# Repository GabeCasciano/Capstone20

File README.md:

# Capstone20

By: Gabriel Casciano, Niharika Shetty, Yasamin Ahmadzadeh, Mai Abdelhameed

------

An autonomous subsystem for a self-driving vehicle. Included in this project are the required software to interface with all of the autonomous sensors, algorithms and feedback loops which utilise the data from the sensors, and the different run-time applications which choose the specific algorithms for the given mode. 

------

## Project Structure

Outlined below is the structure of this repository and locations and purpose of each file, in the directories containing the specific files and the intermediary directories as well there are more files similar to this one which cover the specific files in more detail. Use this project structure below as a map for navigating through this repository.

- **AutonomousPkg**: The custom python package written for this project.
  - **Autonomous**: The top-level directory for the python package.
    - **Modules**: Contains all of the high-level algorithms required for this project.
      - **Obstacle_Detection.py**: This file implements an obstacle detection algorithm that is used to determine if obstacles obstruct the vehicles path, and determine their location relative to the vehicle.
      - **Obstacle_Avoidance.py**: This file implements an obstacle avoidance class and algorithm which simply navigates around the detected obstacle and returns the vehicle to its original path. 
      - **Path_Planning.py**: This file implements the primary path planning algorithm which generates the path, calculates the vehicles error and correction vector relative to the generated path.
      - **Sensor_Fusion.py**: This file implements a practical approach to an extended Kalman filter to fuse together GPS and IMU feedback into stable global coordinates and orientation. 
    - **Run**: Contains all of the run-times.
      - **ManualControl.py**: This file implements manual control via bluetooth controller connected to the base-station computer. It uses an *Arcade control scheme* which is similar to many video games where one joystick controls both power and steering.
      - **GPSAuto.py**: This file implements a simple GPS autonomous, when run the vehicle will navigate to its destination using only the onboard GPS.
      - **SFAuto.py**: This file implements the sensor fusion autonomous, where the vehicle will use its fused IMU and GPS data to navigate from point to point.
      - **FullAuto.py**: This file implements the full autonomous system, where it will use the sensor fusion for position and orientation feedback as well as the LIDAR to detect and avoid obstacles.
    - **Sensors**: Contains all of the sensor interfaces. Each interface implements a thread such that the sensor can be parsed and run concurrently to the rest of the system.
      - **Car**: Contains the interface and test files associated with the car.
        - **PS4_Controller**: Simple python thread used to read a bluetooth controller, meant for use with the manual control run-time.
        - **Car_Interface.py**: This file implements a thread which is used to communicate with the car's on board micro-controller, and provide it with instructions.
        - **Car_Test.py**: This file implements a simple test program which can be used to ensure the the *Car_Interface* is functioning correctly.
      - **GPS**: Contains all of the interface and test files associated with the GPS
        - **GPS_interface.py**: This file implements a thread which is used to parse information from the GPS, the thread is also responsible for formatting the GPS's data into appropriate data structures, providing control functions, as well as provide any conversion functions required. 
        - **GPS_Server.py**: This file implements a simple TCP server which is used to connect to the *GPS_Interface* remotely for control or to view what data is being parsed. 
        - **GPS_Test.py**: This file implements some simple tests to ensure that the *GPS_Interface* is working correctly.
      - **IMU**
        - **IMU_Interface.py**: This file implements a thread which is used to parse information from the IMU, the thread is responsible for formatting the IMU's data into appropriate data structures, as well as providing control functions.
        - **IMU_Server.py**: This file implements a simple TCP server which is used to connect to the *IMU_Interface* remotely for control or to view what data is being parsed.
        - **IMU_Test.py**: This file implements some simple tests to ensure that the *IMU_Interface* is working correctly.
      - **LIDAR**:
        - **LIDAR_Interface.py**: This file implements a thread which is used to parse information from the LIDAR, the thread is responsible for formatting the LIDAR's data into appropriate data structures, as well as providing control functions.
        - **LIDAR_Test.py**: This file implements some simple tests to ensure that the *LIDAR_Interface* is working correctly.
        - **LIDAR_Vis.py**: This file is used to visualise the data that the LIDAR  produces.
  - **build.sh** & **clear.sh**: These two scripts can be used to build the python package, and clear a pre-installed version of the package from the python environment.
  - misc. build and distribution files.
  
- **ControlSystem**: The PCB and software designed and written to test the implementation of our algorithms on a vehicle. This folder also includes all of the mechanical components that were designed for use with the specific car that used during the testing and implementation of this project.

- **Documents**: Implementation notes, diagrams, and documentation.

- **setup.sh**: This script can be used to install the required python packages into a python environment.

------

## Installation

To install the provided python package, python must first be [downloaded & installed](https://www.python.org/ftp/python/3.9.4/Python-3.9.4.tar.xz). 

**From snap:**

```bash
sudo add-apt-repository ppa:deadsnakes/ppa
sudo apt update
sudo apt install python3.9
```

**From source:**

```bash
wget -o https://www.python.org/ftp/python/3.9.4/Python-3.9.4.tar.xz
tar xf Python-3.9.4
cd Python-3.9.4/configure
make
sudo make install
```

------

After completing the installation of python navigate to the top-level folder of this repository (this folder) and run the following script which contains all the required commands to build and install the python package in your local python environment, the package can also be installed in a python venv.

If the folder has not yet been downloaded it can be cloned with git:

```bash
git clone https://github.com/GabeCasciano/Capstone20.git
```

After that:

```bash
cd Capstone20/
./setup.sh
```

------

## Running

After everything has been installed into the local python environment, running is as simple as calling the files, there are 2 ways in which this can be done

**Option 1**:

This option will run the run-time algorithm from the version installed in the local python environment

```bash
python3 -m Autonomous.Run.FullAuto
```

**Option 2**:

This option will run the run-time algorithm directly from the script itself:

```bash
cd Capstone20/AutonomousPkg/Autonomous/Run
python3 FullAuto.py
```

------

## Extending this package

Should you desire to fork this repository to continue our work or implement you own run-time algorithms, simply put the .py file in the folder `Capstone20/AutonomousPkg/Autonomous/Run`. Although technically the run-time algorithms can be run from any directory on your computer as the package installed in the local python environment, if the files are included in the *Run* directory they can be executed using the method provided in **Option 1** above.

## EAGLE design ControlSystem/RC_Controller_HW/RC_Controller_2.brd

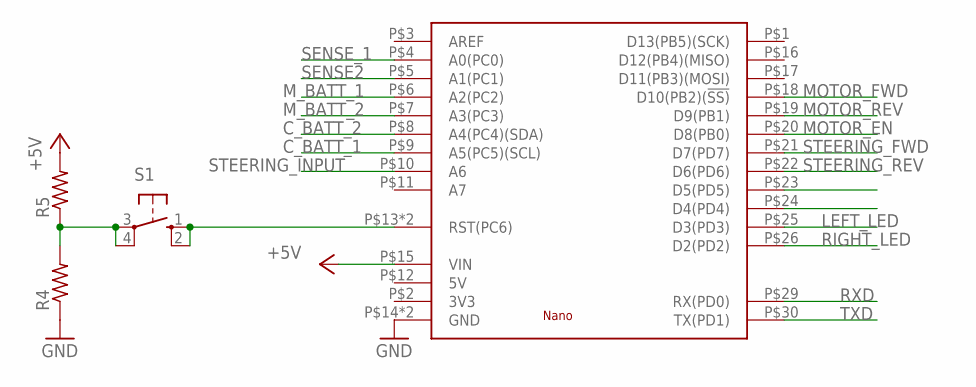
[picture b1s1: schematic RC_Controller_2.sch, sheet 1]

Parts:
R4, R5: R-US_R1206; R1206
S1: 10-XX; B3F-10XX
U$1: ARDUINO_NANO; NANO

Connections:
+5V: R5.2, U$1.P$15 (VIN); also elsewhere on the board
C_BATT_1: U$1.P$9 (A5(PC5)(SCL)); also elsewhere on the board
C_BATT_2: U$1.P$8 (A4(PC4)(SDA)); also elsewhere on the board
GND: R4.1, U$1.P$14 (GND), U$1.P$27 (GND); also elsewhere on the board
LEFT_LED: U$1.P$25 (D3(PD3)); also elsewhere on the board
MOTOR_EN: U$1.P$20 (D8(PB0)); also elsewhere on the board
MOTOR_FWD: U$1.P$18 (D10(PB2)(!SS)); also elsewhere on the board
MOTOR_REV: U$1.P$19 (D9(PB1)); also elsewhere on the board
M_BATT_1: U$1.P$6 (A2(PC2)); also elsewhere on the board
M_BATT_2: U$1.P$7 (A3(PC3)); also elsewhere on the board
unnamed: S1.1 (S), S1.2 (S1), U$1.P$13 (RST(PC6)), U$1.P$28 (RST(PC6))
unnamed: R4.2, R5.1, S1.3, S1.4 (P1)
RIGHT_LED: U$1.P$26 (D2(PD2)); also elsewhere on the board
RXD: U$1.P$29 (RX(PD0)); also elsewhere on the board
SENSE2: U$1.P$5 (A1(PC1)); also elsewhere on the board
SENSE_1: U$1.P$4 (A0(PC0)); also elsewhere on the board
STEERING_FWD: U$1.P$21 (D7(PD7)); also elsewhere on the board
STEERING_INPUT: U$1.P$10 (A6); also elsewhere on the board
STEERING_REV: U$1.P$22 (D6(PD6)); also elsewhere on the board
TXD: U$1.P$30 (TX(PD1)); also elsewhere on the board

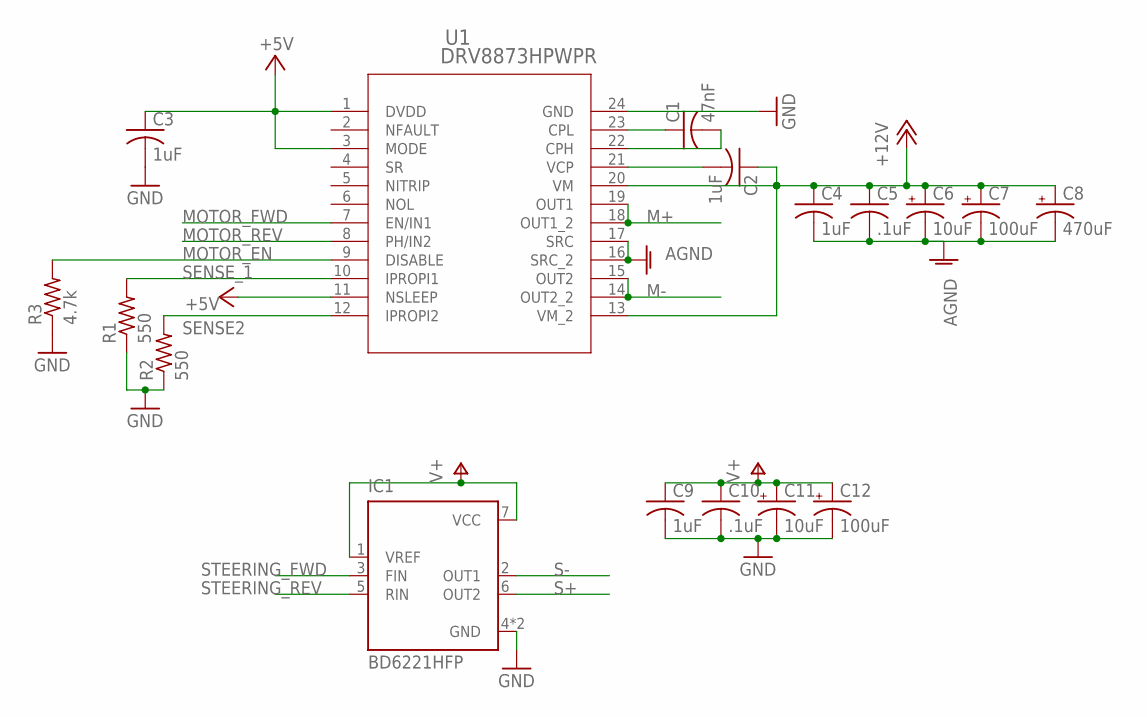
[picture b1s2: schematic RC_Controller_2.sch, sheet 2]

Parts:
C1: 47nF; C1206
C2, C3, C4, C9: 1uF; C1206
C5, C10: .1uF; C1206
C6, C11: 10uF; E2,5-6
C7, C12: 100uF; E2,5-6
C8: 470uF; E2,5-6
IC1: BD6221HFP; HRP7
R1, R2: 550; R1206
R3: 4.7k; R1206
U1: DRV8873HPWPR; PWP24_TEX

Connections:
+5V: C3.1, U1.1 (DVDD), U1.3 (MODE), U1.11 (NSLEEP); also elsewhere on the board
+12V: C2.1, C4.1, C5.1, C6.+, C7.+, C8.+, U1.13 (VM_2), U1.20 (VM); also elsewhere on the board
AGND: C4.2, C5.2, C6.-, C7.-, C8.-, U1.16 (SRC_2), U1.17 (SRC); also elsewhere on the board
GND: C3.2, C9.2, C10.2, C11.-, C12.-, IC1.4 (GND), IC1.P (GND), R1.1, R2.1, R3.1, U1.24 (GND); also elsewhere on the board
M+: U1.18 (OUT1_2), U1.19 (OUT1); also elsewhere on the board
M-: U1.14 (OUT2_2), U1.15 (OUT2); also elsewhere on the board
MOTOR_EN: R3.2, U1.9 (DISABLE); also elsewhere on the board
MOTOR_FWD: U1.7 (EN/IN1); also elsewhere on the board
MOTOR_REV: U1.8 (PH/IN2); also elsewhere on the board
unnamed: C2.2, U1.21 (VCP)
unnamed: C1.1, U1.23 (CPL)
unnamed: C1.2, U1.22 (CPH)
S+: IC1.6 (OUT2); also elsewhere on the board
S-: IC1.2 (OUT1); also elsewhere on the board
SENSE2: R2.2, U1.12 (IPROPI2); also elsewhere on the board
SENSE_1: R1.2, U1.10 (IPROPI1); also elsewhere on the board
STEERING_FWD: IC1.3 (FIN); also elsewhere on the board
STEERING_REV: IC1.5 (RIN); also elsewhere on the board
V+: C9.1, C10.1, C11.+, C12.+, IC1.1 (VREF), IC1.7 (VCC); also elsewhere on the board

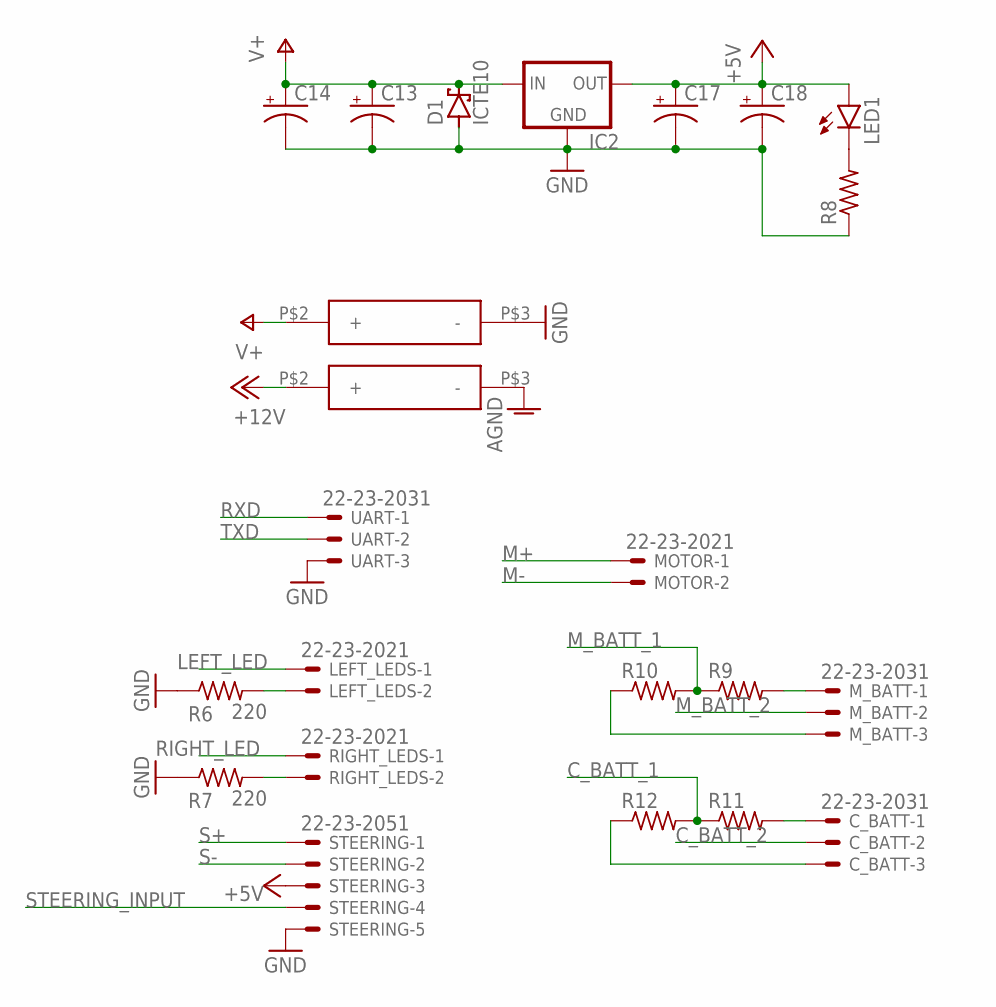
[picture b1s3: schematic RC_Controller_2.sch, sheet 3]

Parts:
C13, C14, C17, C18: CPOL-USE2.5-6; E2,5-6
C_BATT: 22-23-2031
D1: ICTE10; CB417-15
IC2: 78XXL
LED1: LED3MM
LEFT_LEDS: 22-23-2021
MOTOR: 22-23-2021
M_BATT: 22-23-2031
R6, R7: 220; 0207/7
R8, R9, R10, R11, R12: R-US_0207/7; 0207/7
RIGHT_LEDS: 22-23-2021
STEERING: 22-23-2051
U$2, U$3: BATT_TERM
UART: 22-23-2031

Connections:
+5V: C17.+, C18.+, IC2.OUT, LED1.A, STEERING.3; also elsewhere on the board
+12V: U$3.P$2 (+); also elsewhere on the board
AGND: U$3.P$3 (-); also elsewhere on the board
C_BATT_1: R11.1, R12.2; also elsewhere on the board
C_BATT_2: C_BATT.2; also elsewhere on the board
GND: C13.-, C14.-, C17.-, C18.-, D1.A, IC2.GND, R6.1, R7.1, R8.1, STEERING.5, U$2.P$3 (-), UART.3; also elsewhere on the board
LEFT_LED: LEFT_LEDS.1; also elsewhere on the board
M+: MOTOR.1; also elsewhere on the board
M-: MOTOR.2; also elsewhere on the board
M_BATT_1: R9.1, R10.2; also elsewhere on the board
M_BATT_2: M_BATT.2; also elsewhere on the board
unnamed: LEFT_LEDS.2, R6.2
unnamed: R7.2, RIGHT_LEDS.2
unnamed: LED1.K (C), R8.2
unnamed: M_BATT.1, R9.2
unnamed: C_BATT.1, R11.2
unnamed: C_BATT.3, R12.1
unnamed: M_BATT.3, R10.1
RIGHT_LED: RIGHT_LEDS.1; also elsewhere on the board
RXD: UART.1; also elsewhere on the board
S+: STEERING.1; also elsewhere on the board
S-: STEERING.2; also elsewhere on the board
STEERING_INPUT: STEERING.4; also elsewhere on the board
TXD: UART.2; also elsewhere on the board
V+: C13.+, C14.+, D1.C, IC2.IN, U$2.P$2 (+); also elsewhere on the board

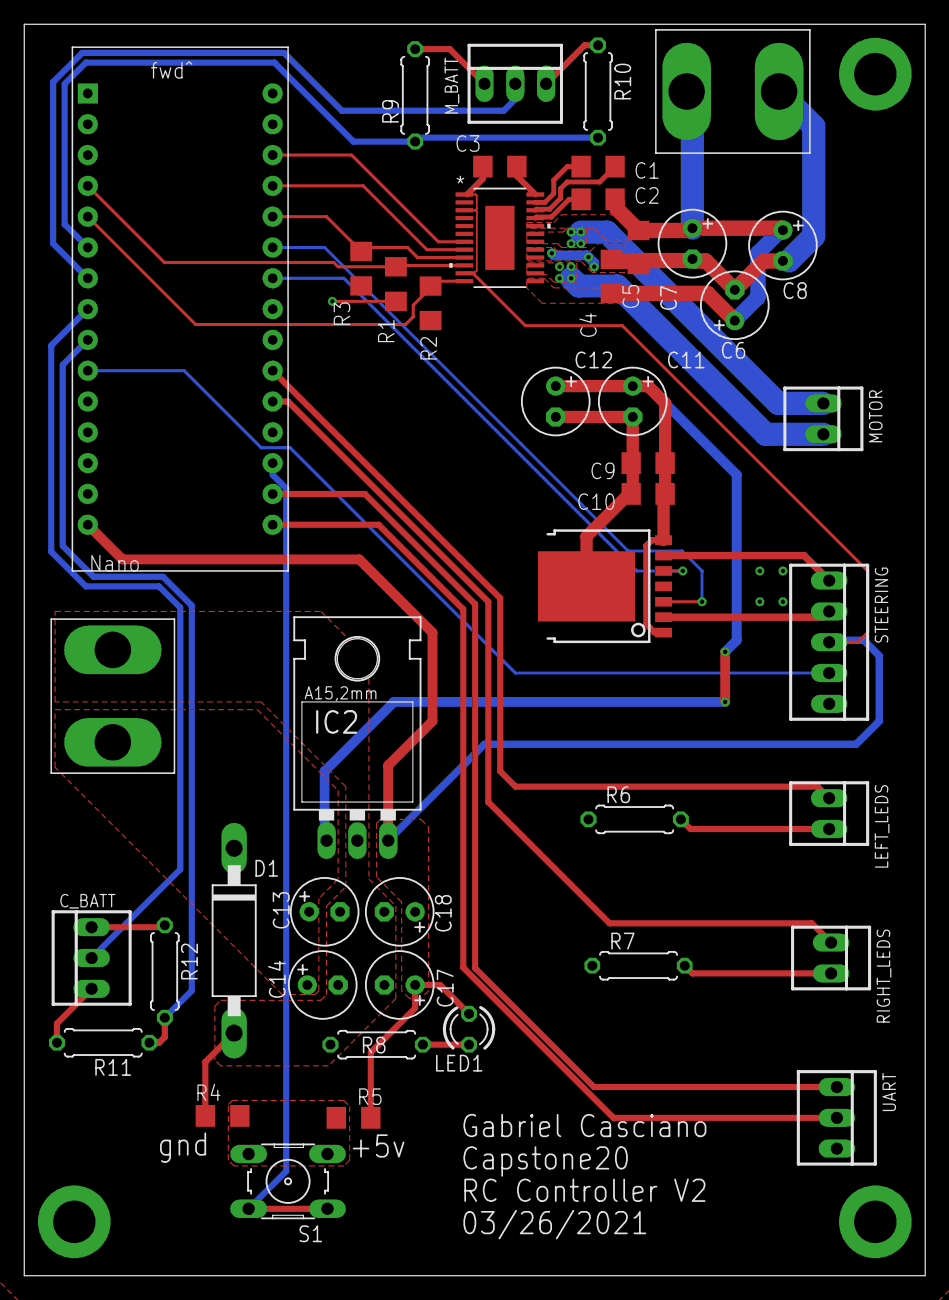
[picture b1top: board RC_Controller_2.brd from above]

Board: 2 copper layers, 74.3 x 103.2 mm, 44 parts (0 on the bottom side), 37 nets.

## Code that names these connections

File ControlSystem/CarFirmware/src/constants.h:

#define NAME "CarFirmware"
#define VERSION "1.0.0"

#define RIGHT_LED 2
#define LEFT_LED 3
#define STEERING_REV 6
#define STEERING_FWD 7
#define MOTOR_EN 8 // active low
#define MOTOR_REV 9
#define MOTOR_FWD 10

#define STEERING_IN A6

// Serial constants 

#define SERIAL_BAUD 9600

#define PACKET_SIZE 64
#define MIN_SIZE 2

#define HS_1 'G'
#define HS_2 'c'

#define TERMINATOR ';'

// Motor constants
#define MOTOR_OFFSET 0
#define MAX_MOTOR_SPEED 255
#define MIN_MOTOR_SPEED 50

// Steering constants
#define MAX_STEERING_ANGLE 30
#define MAX_STEERING_SIG 775
#define MIN_STEERING_ANGLE -30
#define MIN_STEERING_SIG 300
#define MIN_STEERING_SPEED -255
#define MAX_STEERING_SPEED 255
#define STR_SPEED 100
#define STEERING_OFFSET 30
#define STR_KP 1
#define STR_KD 1
#define STR_KI 1
#define STR_SF 5

// Led constants
#define FLASH_DURATION 2000
#define NUM_FLASHES 4

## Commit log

2020-11-09 just some place holders
2020-11-10 begun the GPS interface, made some notes on the NMEA protocol and useful command sentences
2020-11-11 most of the functionality is in there, now requires testing. Also notes and documentation are included
2020-11-11 cleaning up a bit
2020-11-11 cleaning on main
2020-11-11 initializing IMU branch
2020-11-11 initializing LIDAR branch
2020-11-11 Added invoices to main
2020-11-20 gps interface is in a working state
2020-11-20 coming along, got the device to spit out data
2020-11-20 notes
2020-11-20 cleaning up
2021-01-15 organizing
2021-01-15 updated docs
2021-01-19 added some more notes
2021-01-19 cleaning
2021-01-19 added sensor fusion notes
2021-01-19 begun working on the IMU interface
2021-01-20 mostly finished the interface, needs to be tested
2021-01-27 added stop thread, and begun testing
2021-01-27 added stop_thread to GPS lib
2021-01-27 reading sensor just fine
2021-01-27 cleaning up a little, and doing some planning
2021-01-28 added some planning notes to get done
2021-01-31 basic visualization+filter implemented
2021-01-31 updated buffer rate
2021-02-01 path planning implementation
2021-02-03 working on IMU & GPS data server to interface with demo UI
2021-02-03 testing new PAT and adding GPS data server
2021-02-04 gps data server
2021-02-18 not sure if the GPS is working properly, need to test
2021-02-18 started the sensor fusion
2021-02-18 cleaned up imu calculations, added calibration functions
2021-02-18 added exit function for imu and gps
2021-02-18 added a new notes doc
2021-02-18 added data flag to gps, and planend out sf
2021-02-24 Segmentation complete
    spits out segment values for each distance point
2021-02-24 small fix and packing
2021-02-24 turned things into a package, run setup.sh to install into python, libs have some errors still
2021-02-24 re-organizing and cleaning
2021-02-25 Updated algorithm
2021-02-26 Tested first quadrant
2021-02-26 Reorganized again, GPS should be like 95% complete besides some unit testing
2021-03-12 redesigned IMU to be more efficient and more pythonic
2021-03-15 obst avoidance folder added
2021-03-17 A bunch of updates to sensor lib
2021-03-17 begun classifying LIDAR
2021-03-18 slope of obstacle
2021-03-19 LIDAR interface should be completed, and thread handler, which needs testing
2021-03-19 Car controller is like 90% bs'ed so far
2021-03-25 worked on the sf, its in a ehhh state, needs lots more work and testing
2021-03-25 Added the joystick class to be used to tele-op the car
2021-03-25 obst not det
2021-03-26 a few chnages, needs fixing
2021-03-26 minor changes
2021-04-02 just checking something out
2021-04-02 LIDAR class should be done
2021-04-02 re-organizing
2021-04-02 worked on setting up the auton pkg, and getting the class ready to be integrated
2021-04-02 layed out new car controller
2021-04-02 Added segments
2021-04-02 small thing
2021-04-03 finished the fsm, needs testing, sensor fusion properties are set and ready to be used
2021-04-03 removed path following and added it path planning, use path planning as a starting point
2021-04-04 in progress
2021-04-05 made some changes to avoidance algo- still need to set up flags
2021-04-06 integrating with sensor fusion
2021-04-06 integrated detection, pls check
2021-04-06 need to do the flag property & run func
2021-04-06 cleaned up some stuff
2021-04-07 interface and controller talk just fine, need to integrate manual control, and bs auto control via fsm
2021-04-07 car talks to computer :), need to merge the controller branch to main
2021-04-07 too lazy to fix merge conflicts so I just manually moved it
2021-04-07 added car firmware, added car controller software, added car hw, added 3d printed parts as well
2021-04-08 small changes
2021-04-09 updated the car firmware
2021-04-09 safety commit
2021-04-09 demo prep1
2021-04-09 demo prep2
2021-04-09 demo prep3
2021-04-09 demo prep4
2021-04-09 demo prep5
2021-04-09 demo prep6
2021-04-16 made a small change in eqn
2021-04-23 commented obst det&avoid
2021-04-24 updated the main readme
2021-04-24 Adding and editting more documentation
2021-04-24 removing unecessary files
2021-04-25 sensor interfaces documents completed
2021-04-25 fixing conflicts2
2021-04-25 fixing conflicts3
2021-04-29 Fixed bugs

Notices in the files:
parts and their libraries:
COPYRIGHT: Copyright (C) 2018 Accelerated Designs. All rights reserved
